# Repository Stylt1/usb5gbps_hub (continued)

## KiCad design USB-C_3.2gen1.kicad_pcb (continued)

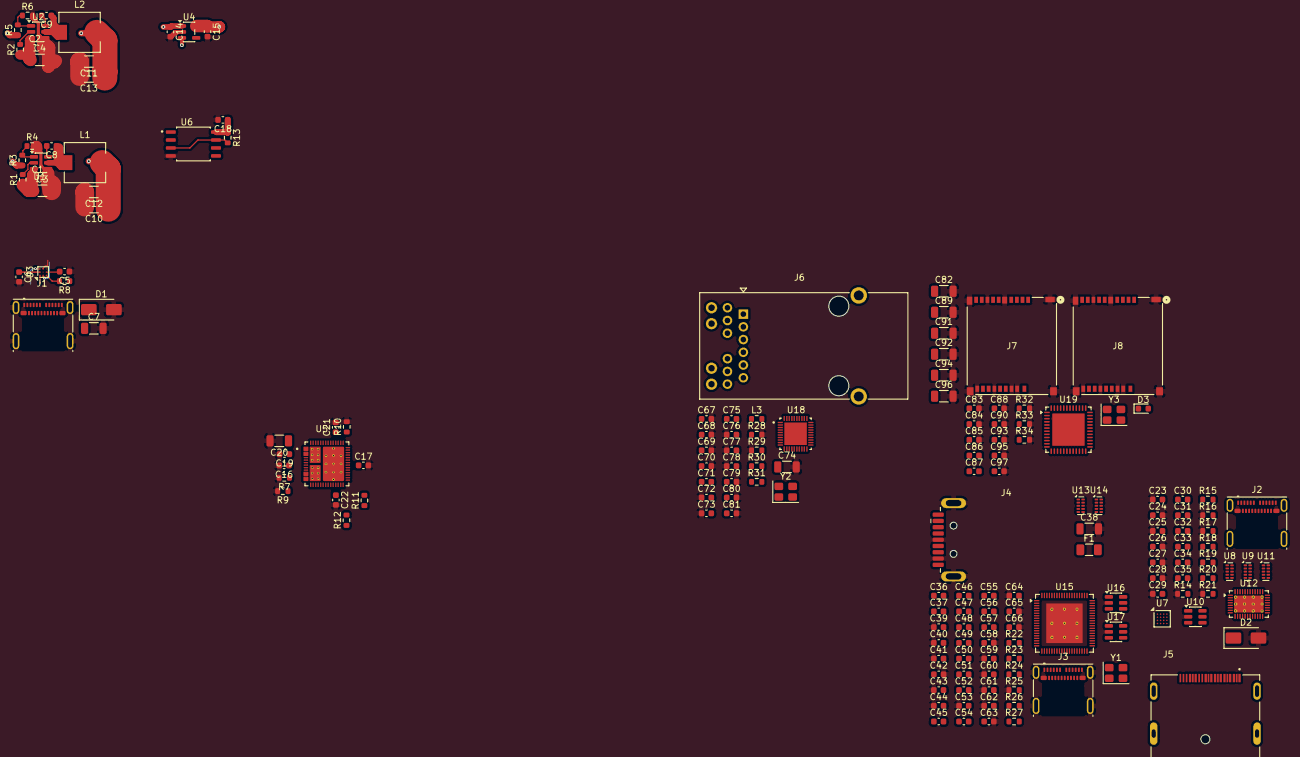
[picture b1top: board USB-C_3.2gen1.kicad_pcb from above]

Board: 8 copper layers, 168 parts (0 on the bottom side), 174 nets.
